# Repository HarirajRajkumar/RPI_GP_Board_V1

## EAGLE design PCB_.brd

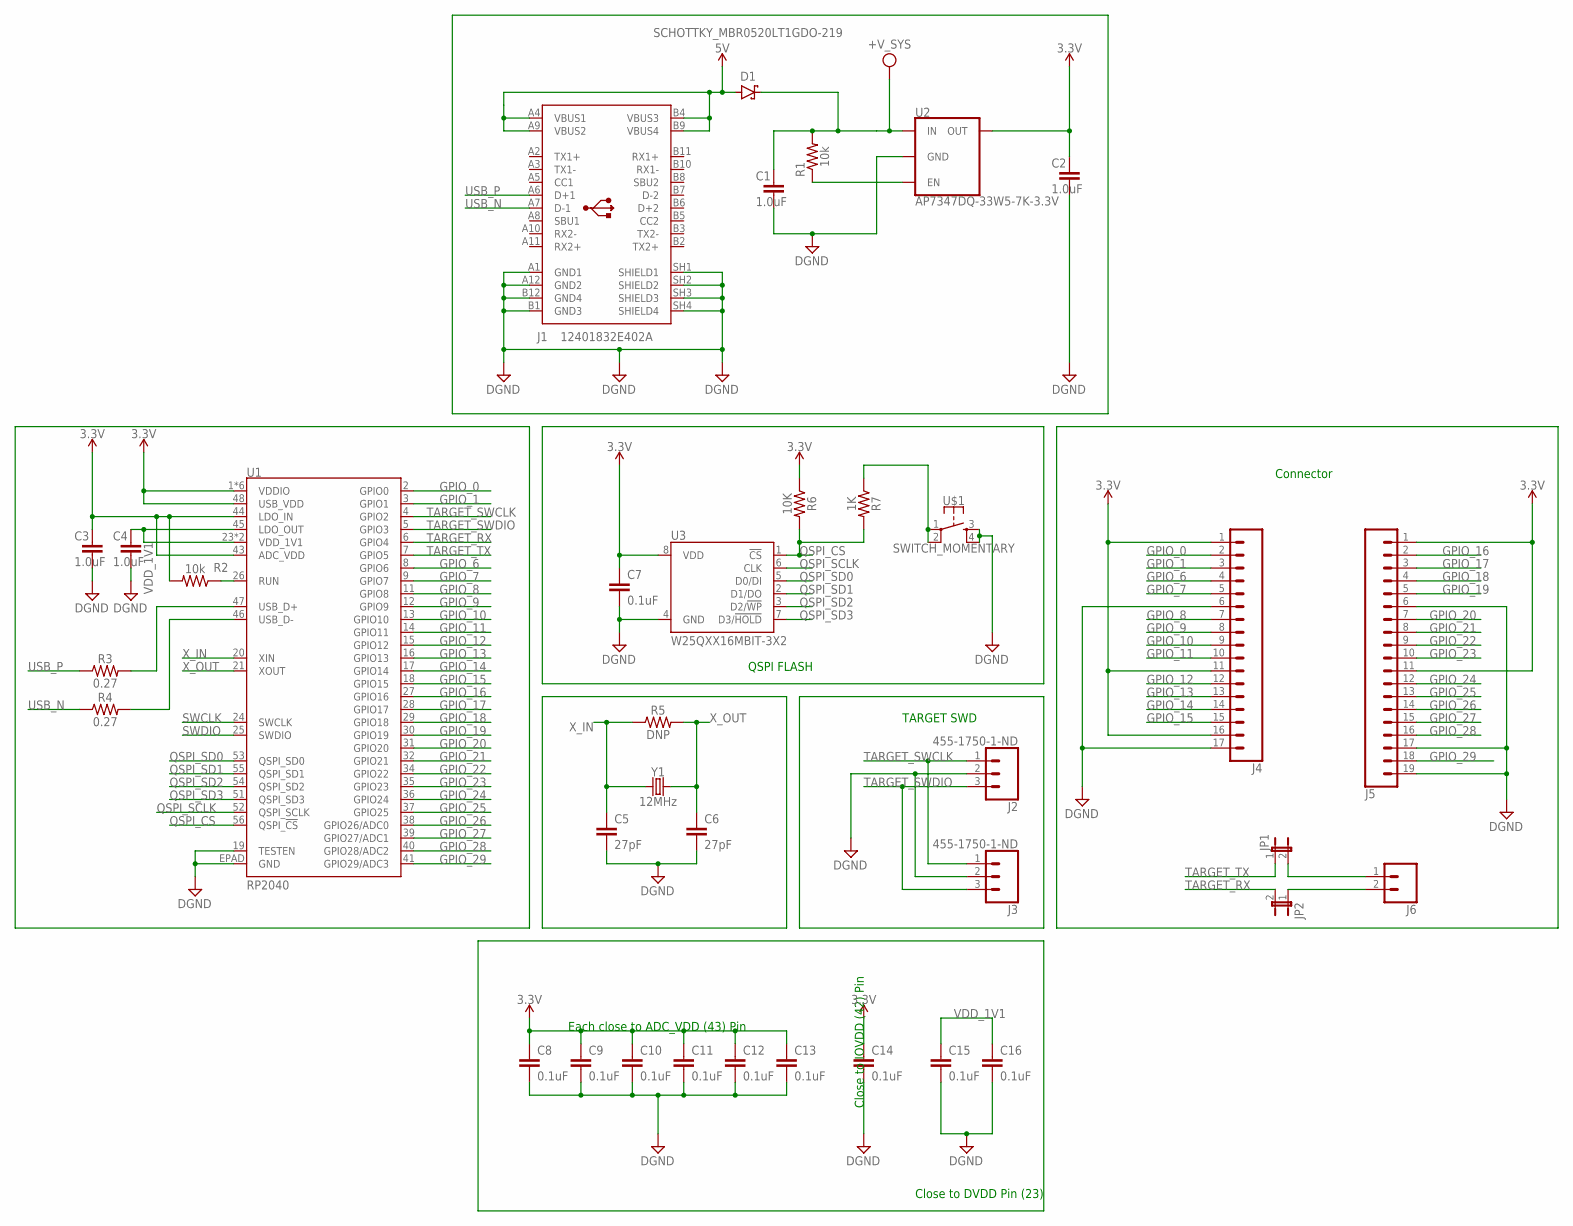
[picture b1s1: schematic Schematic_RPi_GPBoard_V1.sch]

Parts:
C1, C2, C3, C4: 1.0uF; 0603
C5, C6: 27pF; 0603
C7, C8, C9, C10, C11, C12, C13, C14, C15, C16: 0.1uF; 0603
D1: SCHOTTKY_MBR0520LT1GDO-219; SODFL3718X115
J1: 12401832E402A
J2, J3: 455-1750-1-ND; 1X03
J4: CONN_17NOSILK; 1X17_NO_SILK
J5: CONN_19; 1X19
J6: CONN_02; 1X02
JP1, JP2: JUMPER-2SMD-NC; SJ_2S
R1, R2: 10k; AXIAL-0.3
R3, R4: 0.27; 0603
R5: DNP; 0603
R6: 10K; 0603
R7: 1K; 0603
U1: RP2040; QFN-56
U2: AP7347DQ-33W5-7K-3.3V; SOT25
U3: W25QXX16MBIT-3X2; USON-8
U$1: SWITCH_MOMENTARY; SWITCH-MOMENTARY-PTH-6.5MM
Y1: 12MHz; CRYSTAL-SMD-5X3.2-4PAD

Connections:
3.3V: C2.1, C3.1, C7.1, C8.1, C9.1, C10.1, C11.1, C12.1, C13.1, C14.1, J4.1, J4.11, J4.16, J5.1, J5.11, R2.P$2 (2), R6.1, U1.1 (VDDIO), U1.10 (VDDIO), U1.22 (VDDIO), U1.33 (VDDIO), U1.42 (VDDIO), U1.43 (ADC_VDD), U1.44 (LDO_IN), U1.48 (USB_VDD), U1.49 (VDDIO), U2.5 (OUT), U3.8 (VDD)
5V: D1.2 (A), J1.A4 (VBUS1), J1.A9 (VBUS2), J1.B4 (VBUS3), J1.B9 (VBUS4)
+V_SYS: C1.1, D1.1 (C), R1.P$2 (2), U2.1 (IN)
DGND: C1.2, C2.2, C3.2, C4.2, C5.2, C6.2, C7.2, C8.2, C9.2, C10.2, C11.2, C12.2, C13.2, C14.2, C15.2, C16.2, J1.A1 (GND1), J1.A12 (GND2), J1.B1 (GND3), J1.B12 (GND4), J1.SH1 (SHIELD1), J1.SH2 (SHIELD2), J1.SH3 (SHIELD3), J1.SH4 (SHIELD4), J2.2, J3.2, J4.6, J4.17, J5.6, J5.17, J5.19, U1.19 (TESTEN), U1.EPAD (GND), U2.2 (GND), U3.4 (GND), U$1.3, U$1.4
GPIO_0: J4.2, U1.2 (GPIO0)
GPIO_1: J4.3, U1.3 (GPIO1)
GPIO_6: J4.4, U1.8 (GPIO6)
GPIO_7: J4.5, U1.9 (GPIO7)
GPIO_8: J4.7, U1.11 (GPIO8)
GPIO_9: J4.8, U1.12 (GPIO9)
GPIO_10: J4.9, U1.13 (GPIO10)
GPIO_11: J4.10, U1.14 (GPIO11)
GPIO_12: J4.12, U1.15 (GPIO12)
GPIO_13: J4.13, U1.16 (GPIO13)
GPIO_14: J4.14, U1.17 (GPIO14)
GPIO_15: J4.15, U1.18 (GPIO15)
GPIO_16: J5.2, U1.27 (GPIO16)
GPIO_17: J5.3, U1.28 (GPIO17)
GPIO_18: J5.4, U1.29 (GPIO18)
GPIO_19: J5.5, U1.30 (GPIO19)
GPIO_20: J5.7, U1.31 (GPIO20)
GPIO_21: J5.8, U1.32 (GPIO21)
GPIO_22: J5.9, U1.34 (GPIO22)
GPIO_23: J5.10, U1.35 (GPIO23)
GPIO_24: J5.12, U1.36 (GPIO24)
GPIO_25: J5.13, U1.37 (GPIO25)
GPIO_26: J5.14, U1.38 (GPIO26/ADC0)
GPIO_27: J5.15, U1.39 (GPIO27/ADC1)
GPIO_28: J5.16, U1.40 (GPIO28/ADC2)
GPIO_29: J5.18, U1.41 (GPIO29/ADC3)
unnamed: R1.P$1 (1), U2.3 (EN)
unnamed: R2.P$1 (1), U1.26 (RUN)
unnamed: R3.2, U1.47 (USB_D+)
unnamed: R4.2, U1.46 (USB_D-)
unnamed: R7.1, U$1.1, U$1.2
unnamed: J6.1, JP1.2
unnamed: J6.2, JP2.1
QSPI_CS: R6.2, R7.2, U1.56 (QSPI_!CS!), U3.1 (!CS!)
QSPI_SCLK: U1.52 (QSPI_SCLK), U3.6 (CLK)
QSPI_SD0: U1.53 (QSPI_SD0), U3.5 (D0/DI)
QSPI_SD1: U1.55 (QSPI_SD1), U3.2 (D1/DO)
QSPI_SD2: U1.54 (QSPI_SD2), U3.3 (D2/!WP!)
QSPI_SD3: U1.51 (QSPI_SD3), U3.7 (D3/!HOLD!)
SWCLK: U1.24 (SWCLK)
SWDIO: U1.25 (SWDIO)
TARGET_RX: JP2.2, U1.6 (GPIO4)
TARGET_SWCLK: J2.1, J3.1, U1.4 (GPIO2)
TARGET_SWDIO: J2.3, J3.3, U1.5 (GPIO3)
TARGET_TX: JP1.1, U1.7 (GPIO5)
USB_N: J1.A7 (D-1), R4.1
USB_P: J1.A6 (D+1), R3.1
VDD_1V1: C4.1, C15.1, C16.1, U1.23 (VDD_1V1), U1.45 (LDO_OUT), U1.50 (VDD_1V1)
X_IN: C5.1, R5.1, U1.20 (XIN), Y1.1
X_OUT: C6.1, R5.2, U1.21 (XOUT), Y1.3 (2)

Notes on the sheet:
Each close to ADC_VDD (43) Pin
Close to IOVDD (42) Pin
Close to DVDD Pin (23)
TARGET SWD
QSPI FLASH
Connector

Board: 2 copper layers, 37 parts (0 on the bottom side), 52 nets, no tracks yet.

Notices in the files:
parts and their libraries:
SparkFun-Capacitors: Licensing: Creative Commons ShareAlike 4.0 International - https://creativecommons.org/licenses/by-sa/4.0
